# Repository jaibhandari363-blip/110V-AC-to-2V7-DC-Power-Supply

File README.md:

## 110V AC to 2.7V DC Isolated Power Supply

**Tools:** KiCad, LTspice  
**Topology:** Isolated flyback (IRM-10-24) + LM2596S-ADJ buck regulator  
**Output:** 2.7V DC, 200mA  

## What I Built
Designed a two-stage mains power supply from scratch. 
The first stage uses an isolated flyback module (IRM-10-24) 
to step down and isolate the 110V AC input. The second stage 
uses an LM2596S-ADJ adjustable buck regulator to regulate 
the output to 2.7V DC at 200mA.

## Design Process
- Schematic capture and component selection in KiCad
- LTspice simulation to validate circuit behavior
- BOM validation through datasheet analysis
- PCB layout with ERC/DRC verification and GND copper pour
- Bench validation of output voltage regulation and ripple

 ## Schematic

## PCB Layout

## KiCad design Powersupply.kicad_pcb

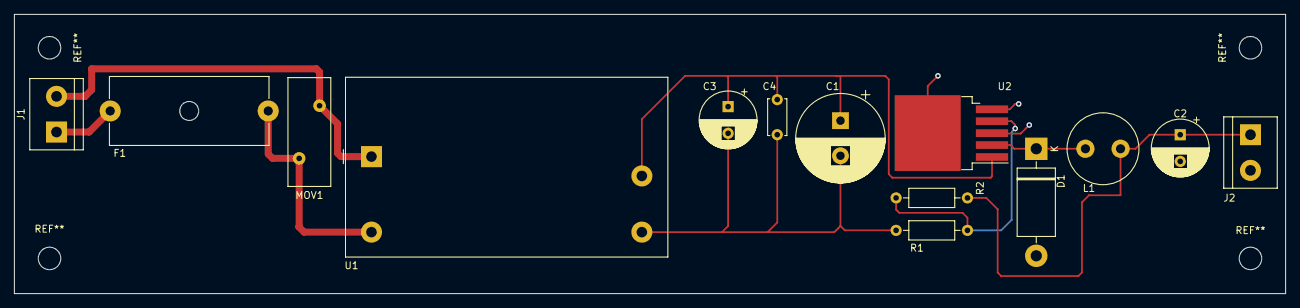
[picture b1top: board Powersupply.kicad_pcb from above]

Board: 2 copper layers, 181.0 x 39.8 mm, 14 parts (0 on the bottom side), 8 nets.

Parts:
C1: 680uF; CP_Radial_D12.5mm_P5.00mm
C2: 220uF; CP_Radial_D8.0mm_P3.80mm
C3: 100uF/35V; CP_Radial_D8.0mm_P3.80mm
C4: 100nF; C_Disc_D5.0mm_W2.5mm_P5.00mm
D1: 1N5820; D_DO-201AD_P15.24mm_Horizontal
F1: 250mA T 250V; Fuseholder_Cylinder-5x20mm_Schurter_0031_8201_Horizontal_Op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
J1: AC_MAINS; TerminalBlock_bornier-2_P5.08mm
J2: DC_OUT_2V7; TerminalBlock_bornier-2_P5.08mm
L1: 100uH; L_Radial_D10.0mm_P5.00mm_Fastron_07M
MOV1: 150VRMS 15mm; RV_Disc_D15.5mm_W6.1mm_P7.5mm
R1: 1k; R_Axial_DIN0207_L6.3mm_D2.5mm_P10.16mm_Horizontal
R2: 1.2k; R_Axial_DIN0207_L6.3mm_D2.5mm_P10.16mm_Horizontal
U1: IRM-10-24; Converter_ACDC_MeanWell_IRM-10-xx_THT
U2: LM2596_ADJ_TRANS; TO-263-5_TabPin3

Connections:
/+24V: C1.1, C3.1, C4.1, U1.4 (+Vo), U2.1 (VIN)
/VOUT: C2.1, J2.1, L1.2, R2.2
GND: C1.2, C2.2, C3.2, C4.2, D1.2 (A), J2.2, R1.1, U1.3 (-Vo), U2.3 (GND), U2.5 (~ON/OFF)
unnamed: D1.1 (K), L1.1, U2.2 (OUT)
unnamed: F1.1, J1.1
unnamed: F1.2, MOV1.1, U1.2 (AC/L)
unnamed: J1.2, MOV1.2, U1.1 (AC/N)
unnamed: R1.2, R2.1, U2.4 (FB)

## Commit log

2026-06-15 Enhance README with project details and design process
    Added detailed project description, tools used, and design process steps.
2026-06-15 Update README with schematic and PCB layout sections
    Added sections for schematic and PCB layout with images.
2026-06-15 Fix PCB Layout image filename in README
